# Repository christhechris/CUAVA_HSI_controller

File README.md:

View this project on [CADLAB.io](https://cadlab.io/project/1621). 

# CUAVA_HSI_controller
eCAD of the CUAVA-1 ISTI payload control board.

This project is licensed under a [Creative Commons Attribution 3.0 Australia License](http://creativecommons.org/licenses/by/3.0/au/)

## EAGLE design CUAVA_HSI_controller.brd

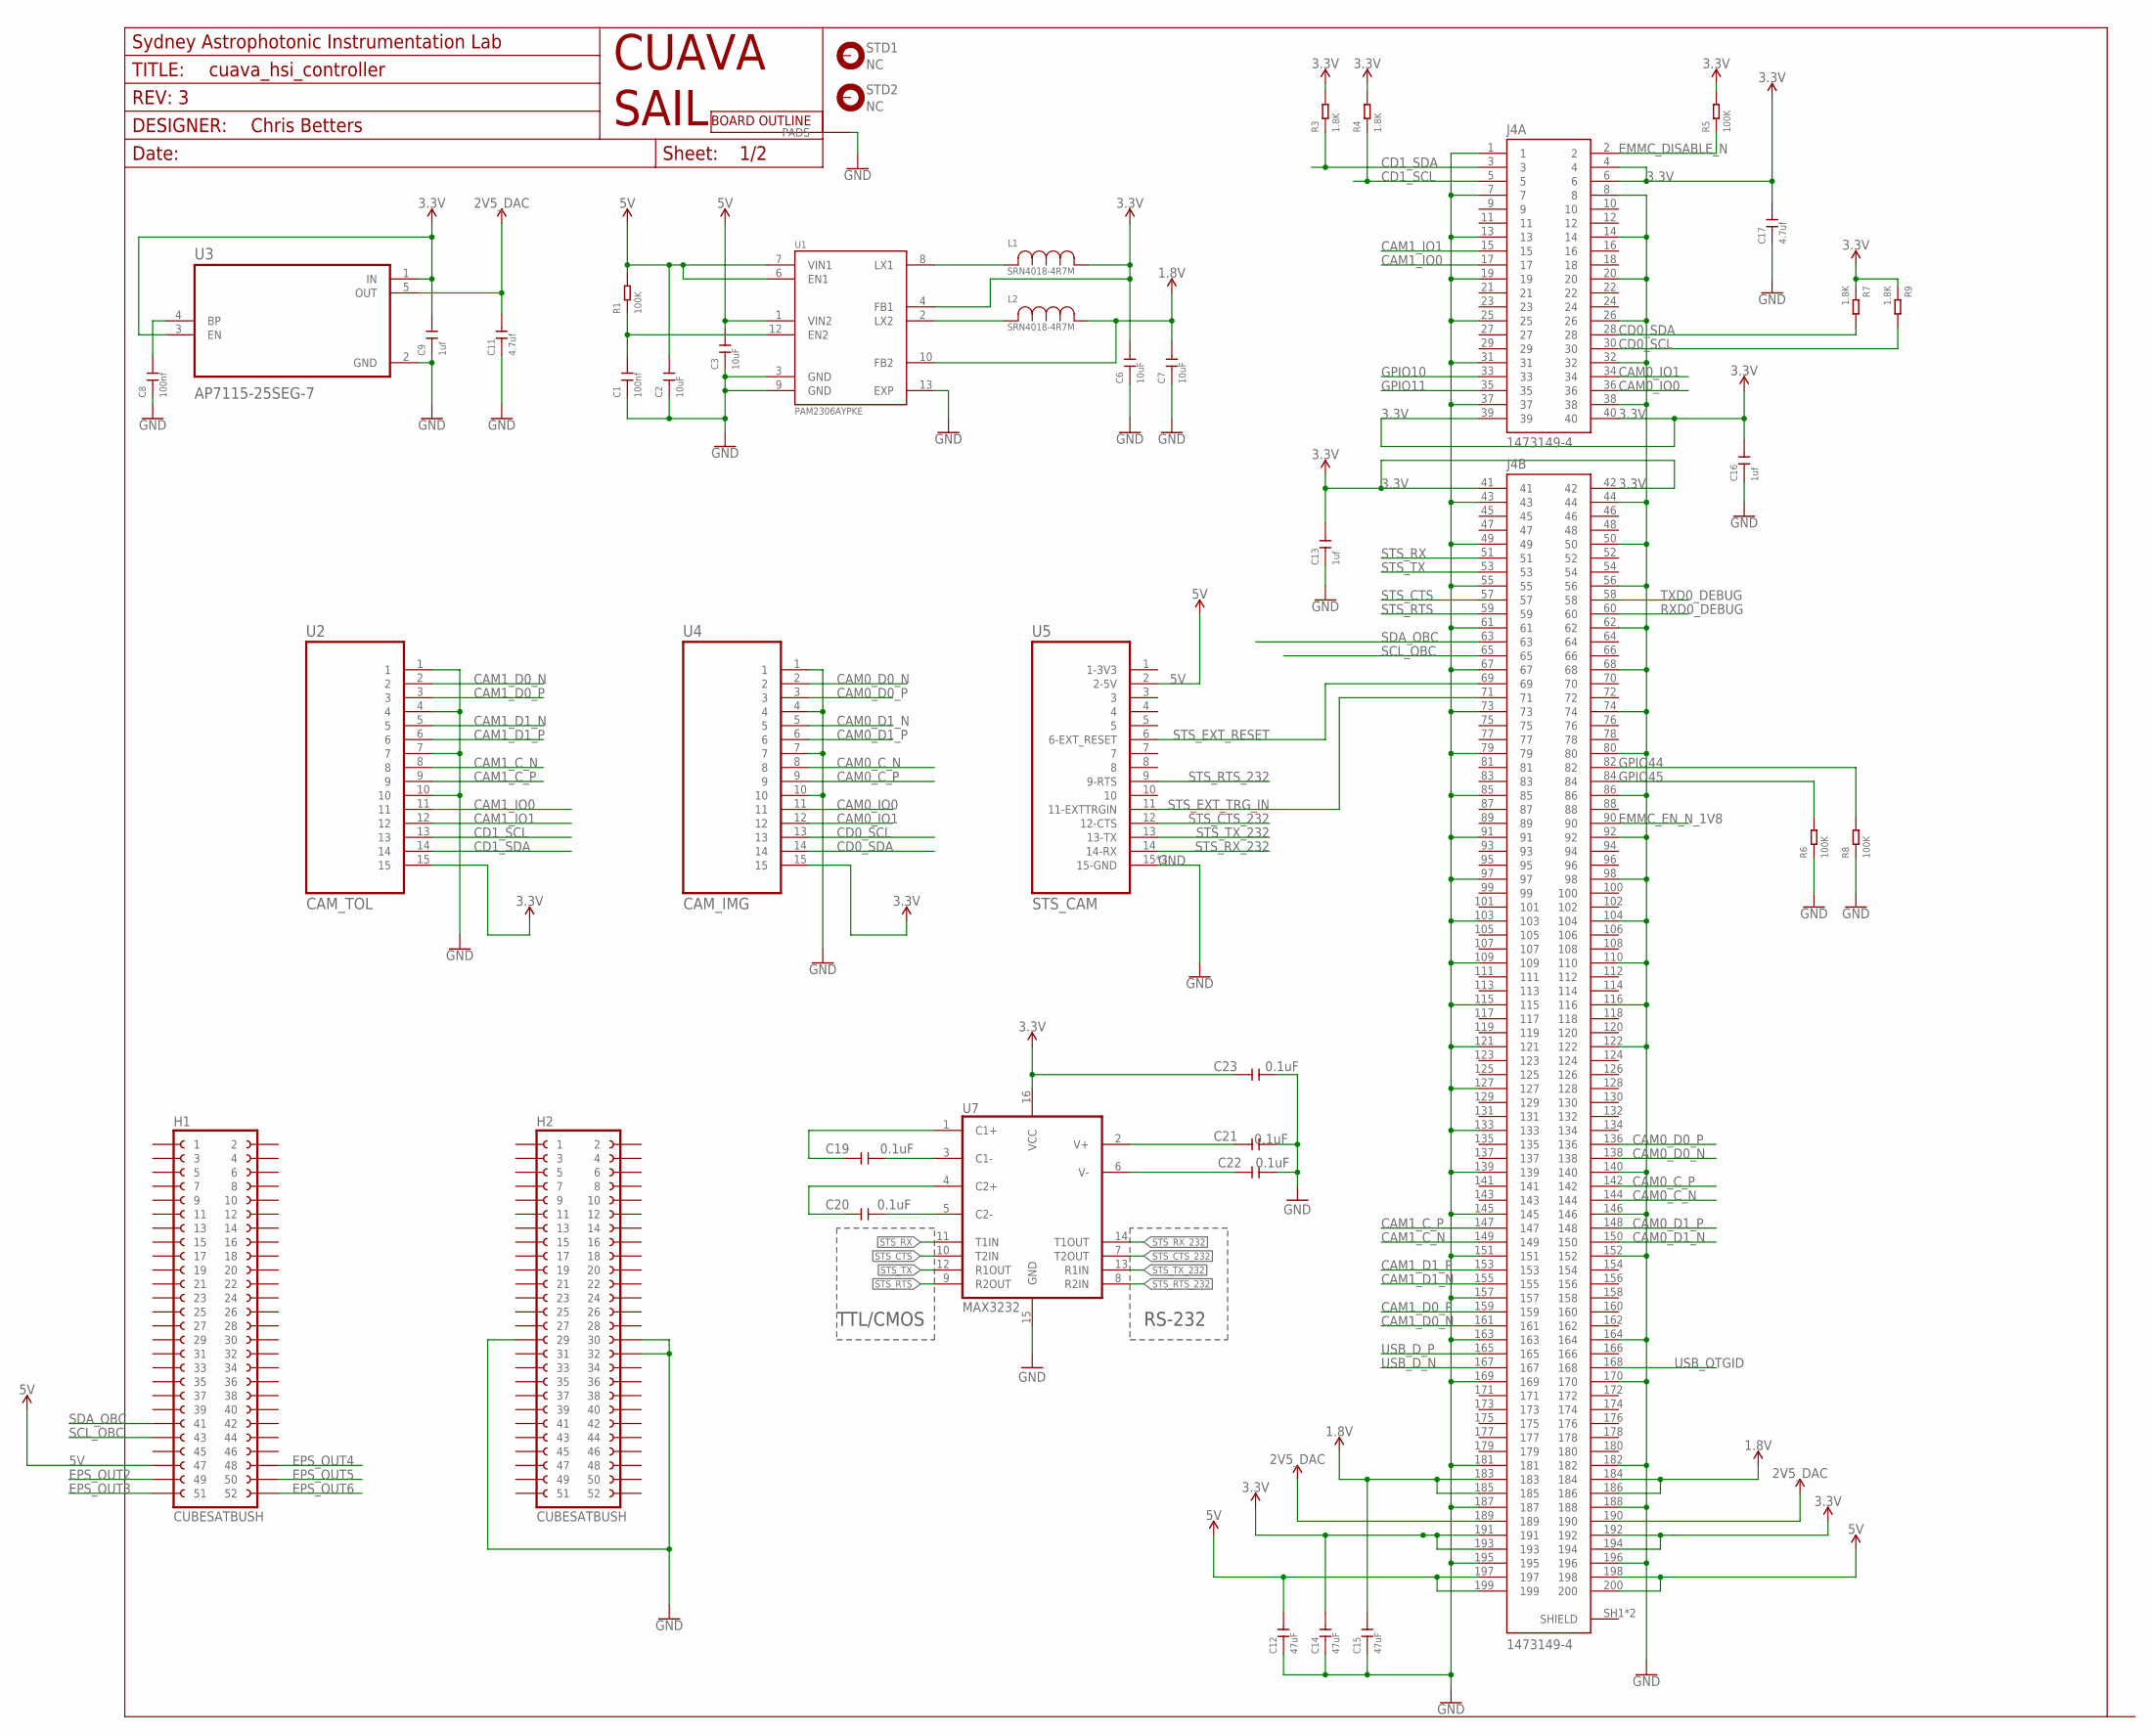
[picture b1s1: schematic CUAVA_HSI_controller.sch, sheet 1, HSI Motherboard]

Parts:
C1, C8: 100nf; C0402K
C2, C3, C6, C7: 10uF; C3216
C9, C13, C16: 1uf; C0402K
C11, C17: 4.7uf; C0603
C12, C14, C15: 47uF; C3216
C19, C20, C21, C22, C23: 0.1uF; C0402K
EDGE1: CUBESAT_BOARD_OUTLINE
FRAME1: SAIL_FRAMEDEFAULT; SAIL_FRAME_DEFAULT
H1, H2: CUBESATBUSH; 2X26HEADER
J4: 1473149-4; TE_1473149-4
L1, L2: SRN4018-4R7M; IND_BOURNS_SRN4018
LOGO1: CUAVA_LOGO
LOGO2: SAIL_LOGO; SAIL_LOGO_VEC_20MM
R1, R5, R6, R8: 100K; R0402
R3, R4, R7, R9: 1.8K; R0402
STD1, STD2: NC; 3,0-PAD
U1: PAM2306AYPKE; SON45P300X300X80-13N
U2: CAM_TOL; FCI_10051922-1510ELF
U3: AP7115-25SEG-7; SOT65P210X110-5N
U4: CAM_IMG; FCI_10051922-1510ELF
U5: STS_CAM; FCI_10051922-1510ELF
U7: MAX3232; TSSOP16

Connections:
1.8V: C7.2, C15.2, J4.183, J4.184, J4.185, J4.186, L2.1, U1.10 (FB2)
2V5: C11.2, J4.189, J4.190, U3.5 (OUT)
3.3V: C6.2, C9.2, C13.2, C14.2, C16.2, C17.2, C23.1, J4.4, J4.6, J4.39, J4.40, J4.41, J4.42, J4.191, J4.192, J4.193, J4.194, L1.1, R3.2, R4.2, R5.2, R7.1, R9.1, U1.4 (FB1), U2.15, U3.1 (IN), U3.3 (EN), U4.15, U7.16 (VCC)
5V: C2.2, C3.2, C12.2, H1.47, J4.197, J4.198, J4.199, J4.200, R1.2, U1.1 (VIN2), U1.6 (EN1), U1.7 (VIN1), U5.2 (2-5V); also elsewhere on the board
C1+: C19.1, U7.1 (C1+)
C1-: C19.2, U7.3 (C1-)
C2+: C20.1, U7.4 (C2+)
C2-: C20.2, U7.5 (C2-)
CAM0_C_N: J4.144, U4.8
CAM0_C_P: J4.142, U4.9
CAM0_D0_N: J4.138, U4.2
CAM0_D0_P: J4.136, U4.3
CAM0_D1_N: J4.150, U4.5
CAM0_D1_P: J4.148, U4.6
CAM0_IO0: J4.36, U4.11
CAM0_IO1: J4.34, U4.12
CAM1_C_N: J4.149, U2.8
CAM1_C_P: J4.147, U2.9
CAM1_D0_N: J4.161, U2.2
CAM1_D0_P: J4.159, U2.3
CAM1_D1_N: J4.155, U2.5
CAM1_D1_P: J4.153, U2.6
CAM1_IO0: J4.17, U2.11
CAM1_IO1: J4.15, U2.12
CD0_SCL: J4.30, R9.2, U4.13
CD0_SDA: J4.28, R7.2, U4.14
CD1_SCL: J4.5, R4.1, U2.13
CD1_SDA: J4.3, R3.1, U2.14
EMMC_DISABLE_N: J4.2, R5.1
EMMC_EN_N_1V8: J4.90
EN2: C1.2, R1.1, U1.12 (EN2)
EPS_OUT2: H1.49; also elsewhere on the board
EPS_OUT3: H1.51
EPS_OUT4: H1.48; also elsewhere on the board
EPS_OUT5: H1.50; also elsewhere on the board
EPS_OUT6: H1.52; also elsewhere on the board
GND: C1.1, C2.1, C3.1, C6.1, C7.1, C8.1, C9.1, C11.1, C12.1, C13.1, C14.1, C15.1, C16.1, C17.1, C21.2, C22.2, C23.2, EDGE1.P$1, EDGE1.P$2, EDGE1.P$3, EDGE1.P$4, H2.29, H2.30, H2.32, J4.1, J4.7, J4.8, J4.13, J4.14, J4.19, J4.20, J4.25, J4.26, J4.31, J4.32, J4.37, J4.38, J4.43, J4.44, J4.49, J4.50, J4.55, J4.56, J4.61, J4.62, J4.67, J4.68, J4.73, J4.74, J4.79, J4.80, J4.85, J4.86, J4.91, J4.92, J4.97, J4.98, J4.103, J4.104, J4.109, J4.110, J4.115, J4.116, J4.121, J4.122, J4.127, J4.133, J4.139, J4.140, J4.145, J4.146, J4.151, J4.152, J4.157, J4.163, J4.164, J4.169, J4.170, J4.181, J4.182, J4.187, J4.188, J4.195, J4.196, R6.1, R8.1, U1.3 (GND), U1.9 (GND), U1.13 (EXP), U2.1, U2.4, U2.7, U2.10, U3.2 (GND), U4.1, U4.4, U4.7, U4.10, U5.15 (15-GND), U5.16 (15-GND), U5.17 (15-GND), U7.15 (GND); also elsewhere on the board
GPIO10: J4.33
GPIO11: J4.35
GPIO44: J4.82, R8.2
GPIO45: J4.84, R6.2
LX1: L1.2, U1.8 (LX1)
LX2: L2.2, U1.2 (LX2)
unnamed: C8.2, U3.4 (BP)
RXD0_DEBUG: J4.60; also elsewhere on the board
SCL_OBC: H1.43, J4.65; also elsewhere on the board
SDA_OBC: H1.41, J4.63; also elsewhere on the board
STS_CTS: J4.57, U7.10 (T2IN)
STS_CTS_232: U5.12 (12-CTS), U7.7 (T2OUT)
STS_EXT_RESET: J4.69, U5.6 (6-EXT_RESET)
STS_EXT_TRG_IN: J4.71, U5.11 (11-EXTTRGIN)
STS_RTS: J4.59, U7.9 (R2OUT)
STS_RTS_232: U5.9 (9-RTS), U7.8 (R2IN)
STS_RX: J4.51, U7.11 (T1IN)
STS_RX_232: U5.14 (14-RX), U7.14 (T1OUT)
STS_TX: J4.53, U7.12 (R1OUT)
STS_TX_232: U5.13 (13-TX), U7.13 (R1IN)
TXD0_DEBUG: J4.58; also elsewhere on the board
USB_D_N: J4.167; also elsewhere on the board
USB_D_P: J4.165; also elsewhere on the board
USB_OTGID: J4.168
V+: C21.1, U7.2 (V+)
V-: C22.1, U7.6 (V-)

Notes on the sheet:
RS-232
TTL/CMOS

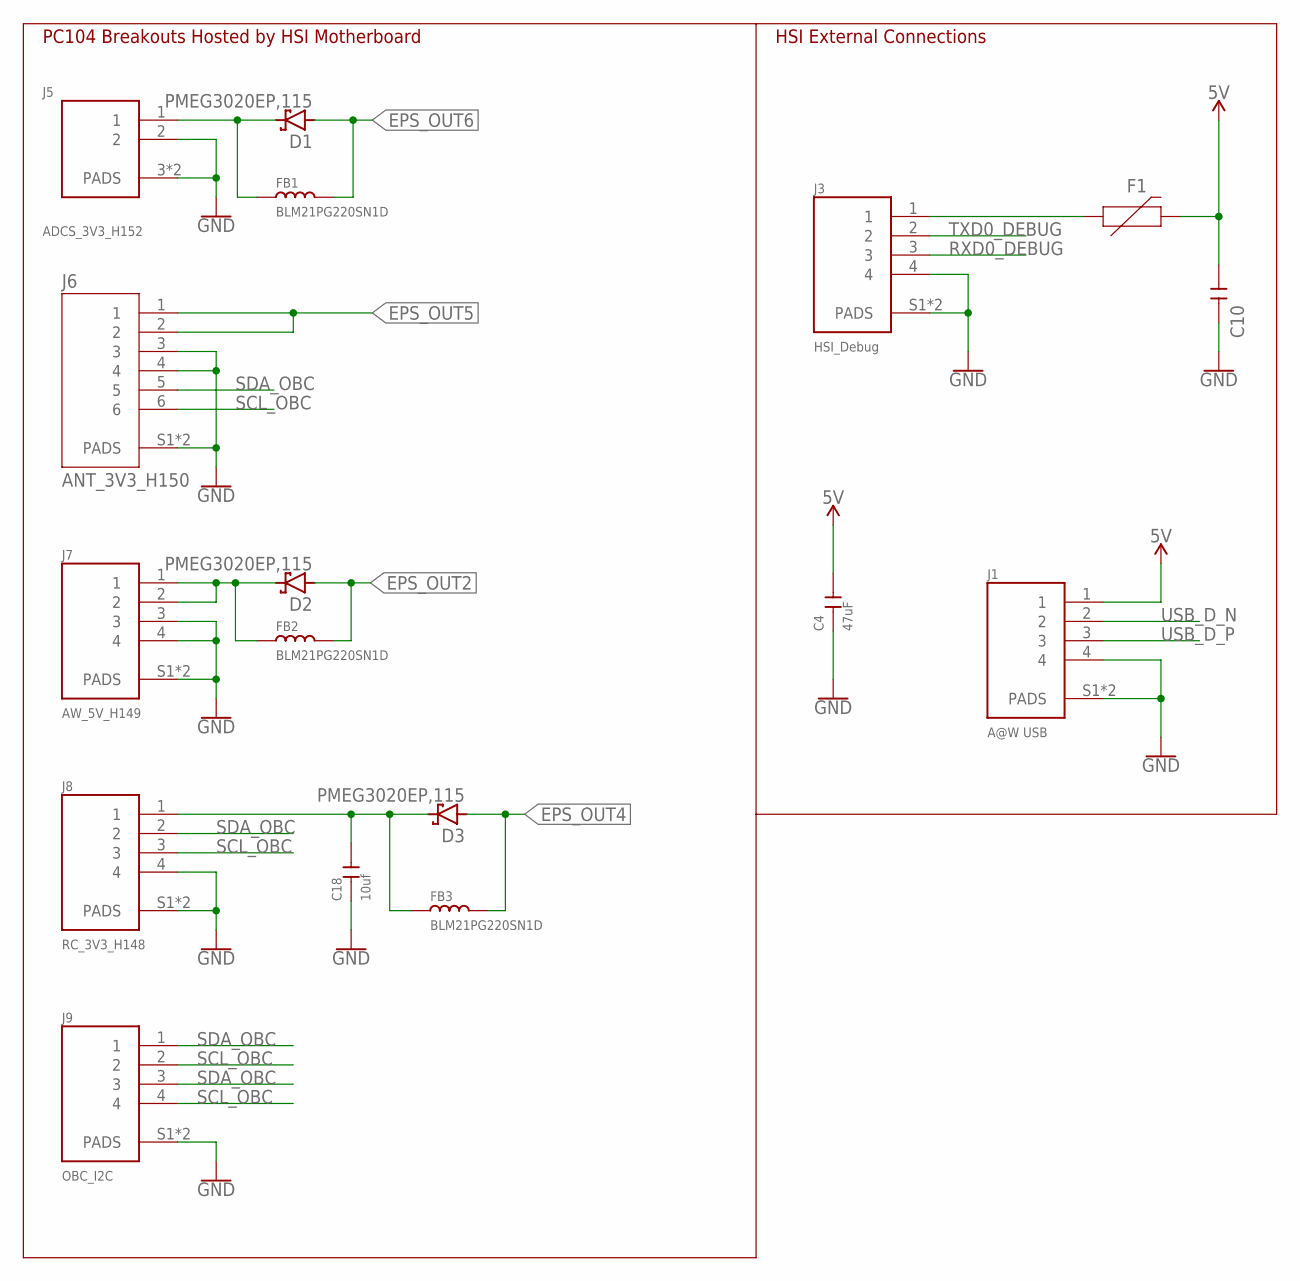
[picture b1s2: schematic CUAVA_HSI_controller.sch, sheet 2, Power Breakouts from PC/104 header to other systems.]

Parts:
C4, C10: 47uF; C3216
C18: 10uf; C2012
D1, D2, D3: PMEG3020EP,115; SODFL4725X110N
F1: MF-MSMF200-2; FUSM4632X85
FB1, FB2, FB3: BLM21PG220SN1D; C0805
J1: A@W USB; MOLEX_0532610471
J3: HSI_Debug; MOLEX_0532610471
J5: ADCS_3V3_H152; MOLEX_0532610271
J6: ANT_3V3_H150; MOLEX_0532610671
J7: AW_5V_H149; MOLEX_0532610471
J8: RC_3V3_H148; MOLEX_0532610471
J9: OBC_I2C; MOLEX_0532610471

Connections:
5V: C4.2, C10.1, F1.2, J1.1; also elsewhere on the board
A@W_5V0: D2.C, FB2.1, J7.1, J7.2
ADCS_3V3: D1.C, FB1.1, J5.1
EPS_OUT2: D2.A, FB2.2; also elsewhere on the board
EPS_OUT4: D3.A, FB3.2; also elsewhere on the board
EPS_OUT5: J6.1, J6.2; also elsewhere on the board
EPS_OUT6: D1.A, FB1.2; also elsewhere on the board
GND: C4.1, C10.2, C18.1, J1.4, J1.S1 (PADS), J1.S2 (PADS), J3.4, J3.S1 (PADS), J3.S2 (PADS), J5.2, J5.3 (PADS), J5.4 (PADS), J6.3, J6.4, J6.S1 (PADS), J6.S2 (PADS), J7.3, J7.4, J7.S1 (PADS), J7.S2 (PADS), J8.4, J8.S1 (PADS), J8.S2 (PADS), J9.S1 (PADS), J9.S2 (PADS); also elsewhere on the board
HSI_DEBUG_V: F1.1, J3.1
RC_3V3: C18.2, D3.C, FB3.1, J8.1
RXD0_DEBUG: J3.3; also elsewhere on the board
SCL_OBC: J6.6, J8.3, J9.2, J9.4; also elsewhere on the board
SDA_OBC: J6.5, J8.2, J9.1, J9.3; also elsewhere on the board
TXD0_DEBUG: J3.2; also elsewhere on the board
USB_D_N: J1.2; also elsewhere on the board
USB_D_P: J1.3; also elsewhere on the board

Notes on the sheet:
PC104 Breakouts Hosted by HSI Motherboard
HSI External Connections

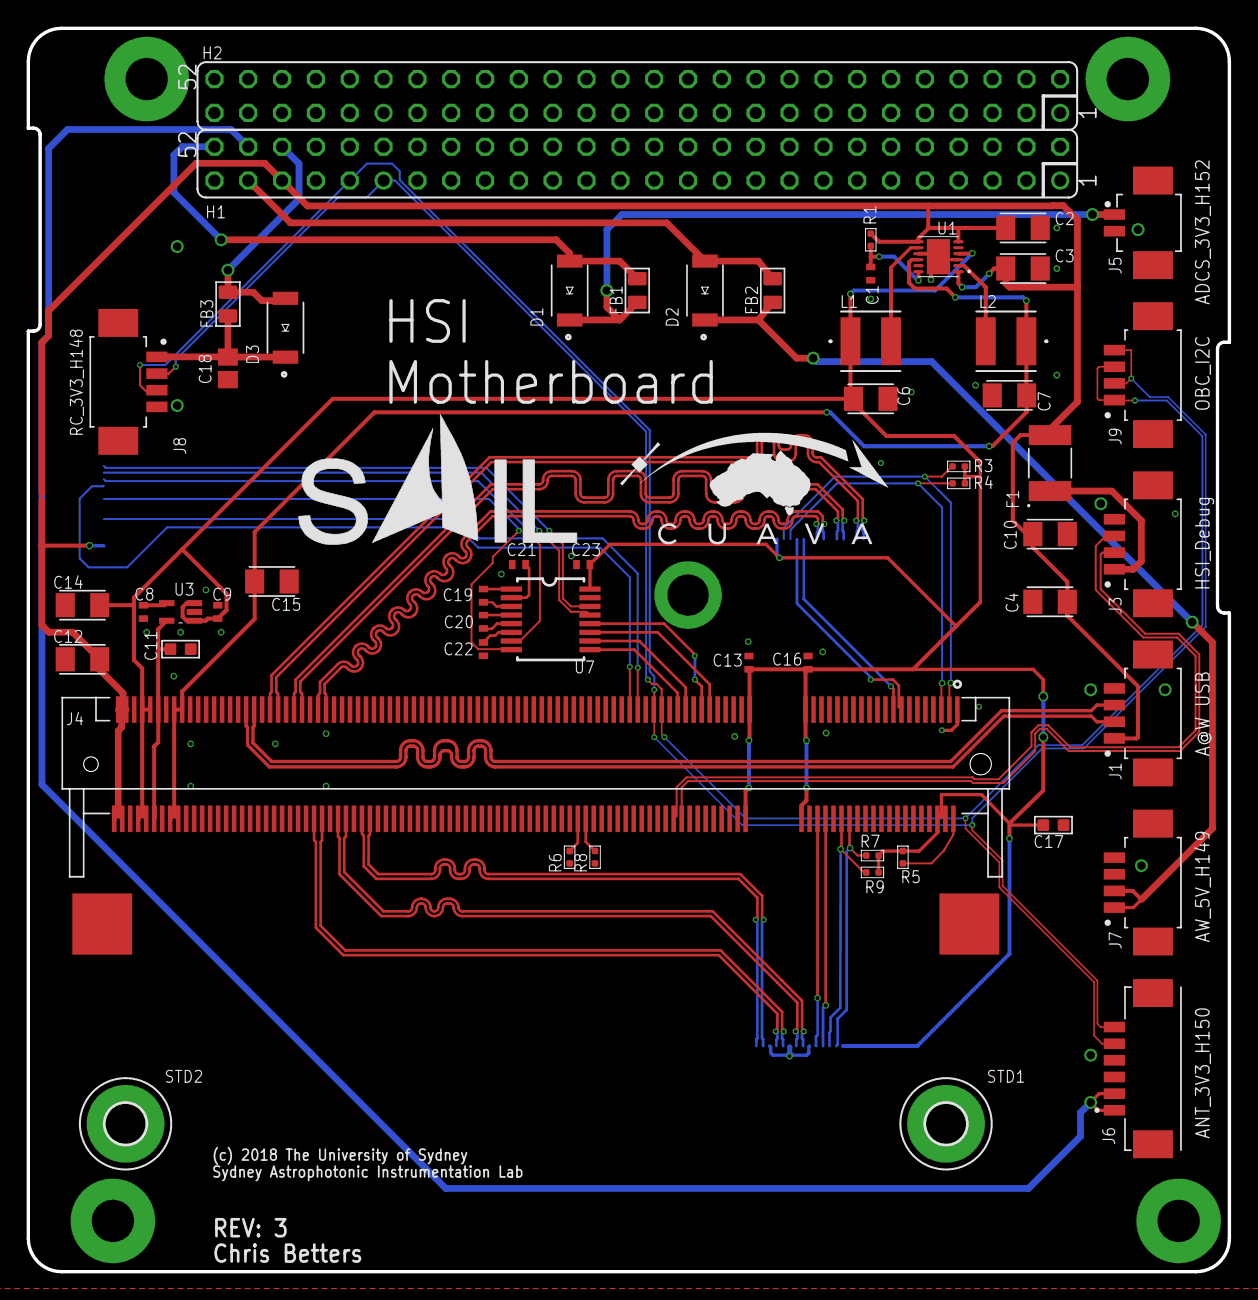
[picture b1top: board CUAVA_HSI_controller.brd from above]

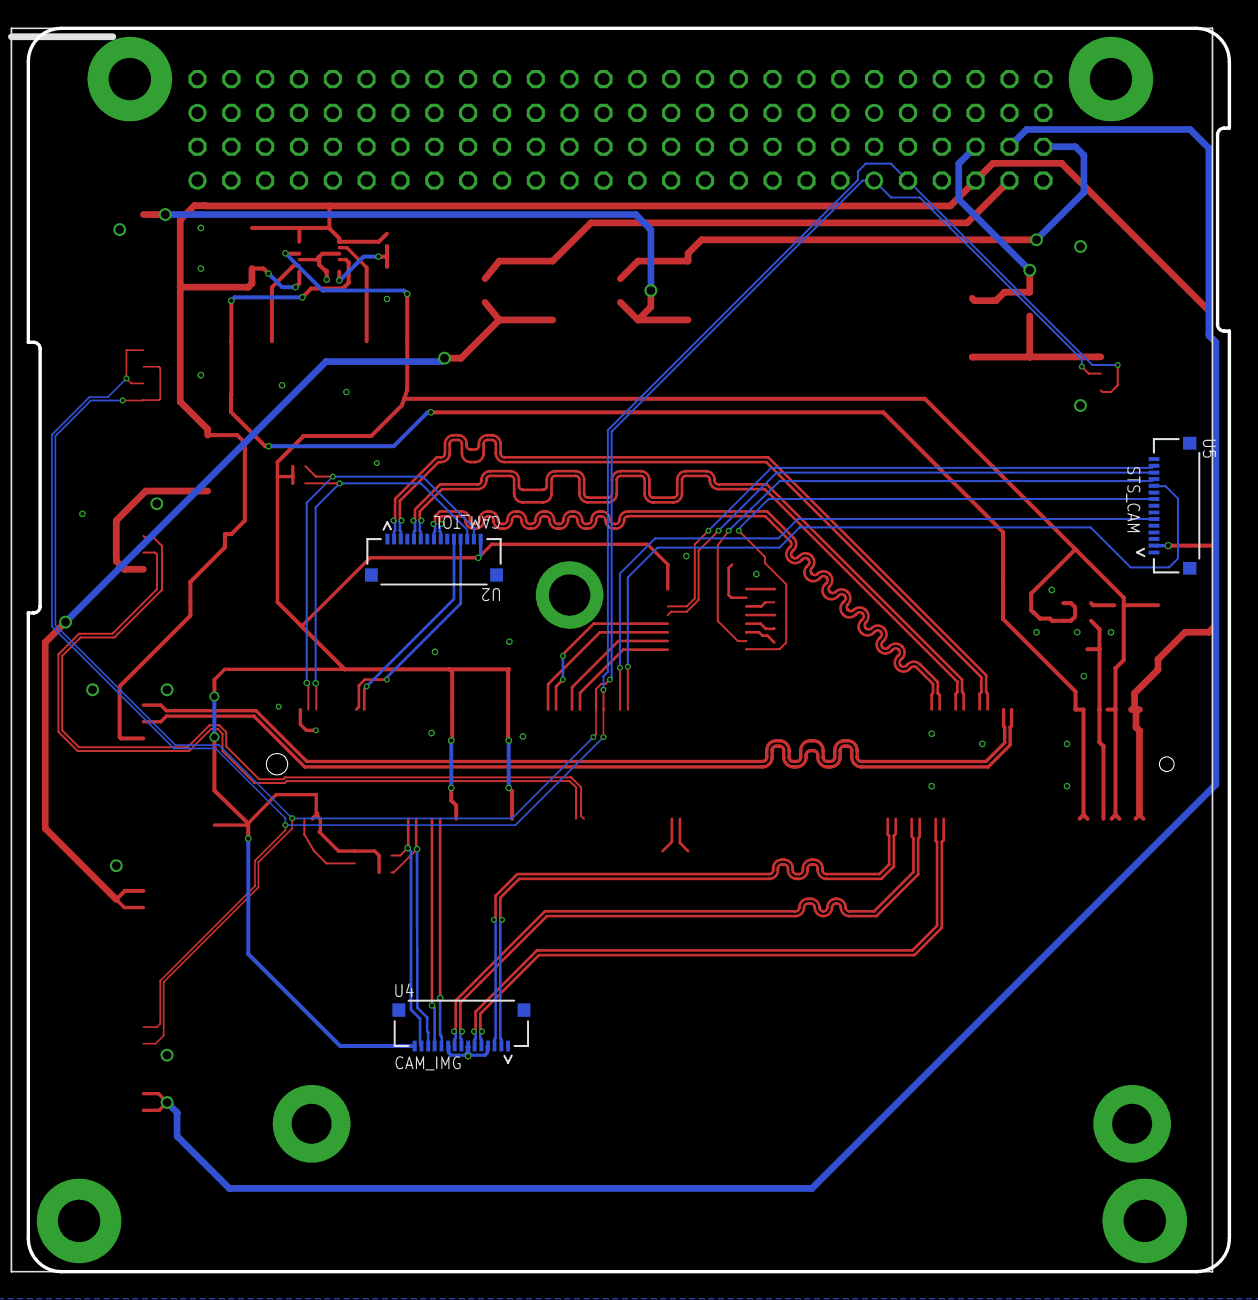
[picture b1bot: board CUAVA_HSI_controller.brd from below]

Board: 4 copper layers, 90.2 x 93.3 mm, 61 parts (4 on the bottom side), 62 nets.

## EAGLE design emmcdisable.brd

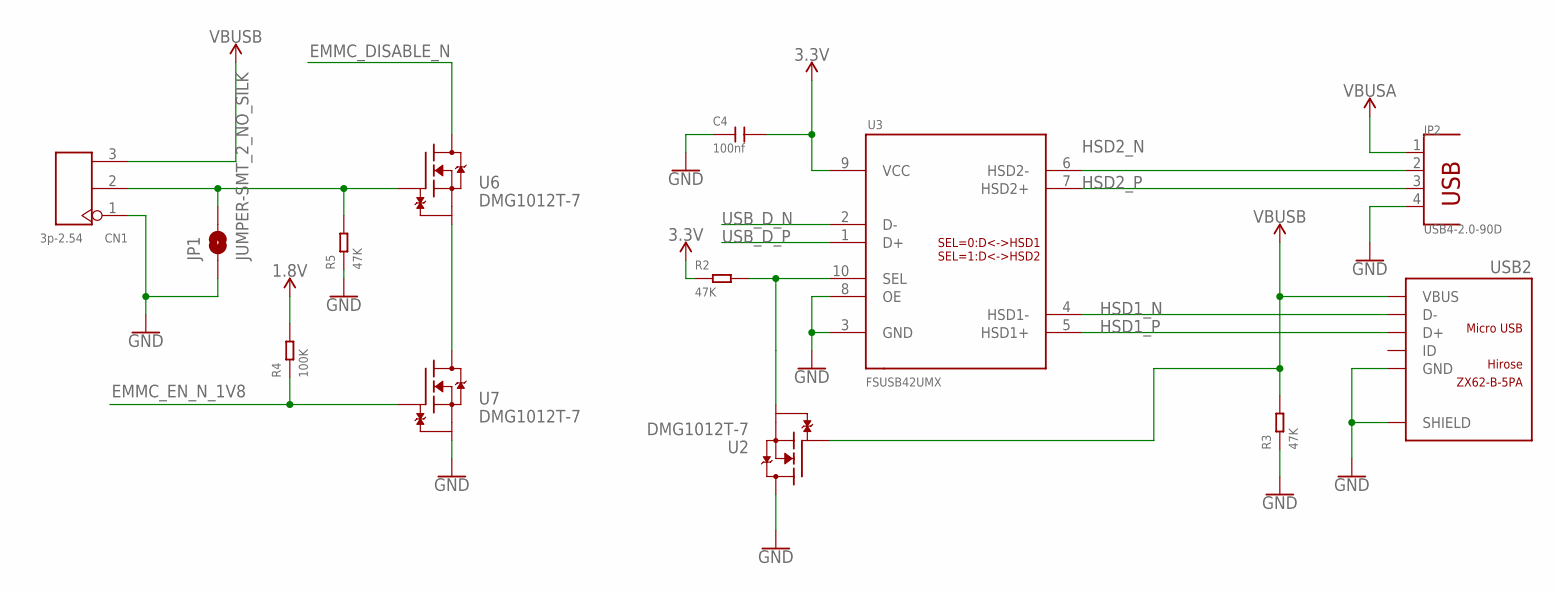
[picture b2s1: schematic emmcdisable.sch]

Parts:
C4: 100nf; C0402K
CN1: 3p-2.54; H3-2.54
JP1: JUMPER-SMT_2_NO_SILK; SMT-JUMPER_2_NO_SILK
JP2: USB4-2.0-90D; USB4+2P-2.0-90D
R2, R3, R5: 47K; R0402
R4: 100K; R0402
U2, U6, U7: DMG1012T-7; SOT50P175X90-3N
U3: FSUSB42UMX; QFN40P140X180X55-10
USB2: ZX62-B-5PA; MICRO-USB5+6P-SMD-0.65-AB

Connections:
1.8V: R4.2
3.3V: C4.2, R2.1, U3.9 (VCC)
EMMC_DISABLE_N: U6.D
EMMC_EN_N_1V8: R4.1, U7.G
GND: C4.1, CN1.1, JP1.1, JP2.4, R3.1, R5.1, U2.D, U3.3 (GND), U3.8 (OE), U7.S, USB2.5 (GND), USB2.P1 (SHIELD), USB2.P2 (SHIELD), USB2.P3 (SHIELD), USB2.P4 (SHIELD), USB2.P5 (SHIELD), USB2.P6 (SHIELD)
HSD1_N: U3.4 (HSD1-), USB2.2 (D-)
HSD1_P: U3.5 (HSD1+), USB2.3 (D+)
HSD2_N: JP2.2, U3.6 (HSD2-)
HSD2_P: JP2.3, U3.7 (HSD2+)
unnamed: CN1.2, JP1.2, R5.2, U6.G
unnamed: U6.S, U7.D
SEL: R2.2, U2.S, U3.10 (SEL)
USB_D_N: U3.2 (D-)
USB_D_P: U3.1 (D+)
VBUSA: JP2.1
VBUSB: CN1.3, R3.2, U2.G, USB2.1 (VBUS)

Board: 2 copper layers, 13 parts (0 on the bottom side), 11 nets, no tracks yet.

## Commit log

2019-02-27 init commit
2019-02-27 Backlink to CADLAB.io has been added.
2019-02-27 fix ignores
2019-03-20 - remove camera and i2c swtich. - add STS connector and wire to serial
2019-04-15 add alt OBC interface via SPI to i2C bridge
2019-04-18 ordered - https://factory.macrofab.com/order/10x65av/overview
2019-08-22 - adding break out connecting for rad counter, air wave power backup, and HSI debug breakout - removing SPI option
2019-08-22 - update gitignore
2019-11-19 - rs232 converter for spec. - adjust breakouts for sat
2019-11-20 - ordered version Macrofab order r6rnxag
2022-03-27 Create LICENSE

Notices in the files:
README.md:
License: CC BY 3.0 AU
parts and their libraries:
RPI_CAM: (c) 2018 The University of Sydney
SparkFun-Aesthetics: Licensing: CC v3.0 Share-Alike You are welcome to use this library for commercial purposes.
SparkFun-PowerSymbols: Licensing: Creative Commons ShareAlike 4.0 International - https://creativecommons.org/licenses/by-sa/4.0
